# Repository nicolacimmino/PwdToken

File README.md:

# PwdToken

## Introduction

This started as a hardware implementation of a piece of paper with your password on it and, in some respect, it sill is. So use it with judgment! I toyed at first with the idea mostly of having something to type the WiFi password on new devices or for guests.

Once the novelty of the first quick implementation wore out, I started to wonder how I could make this at least reasonably secure. In its current incarnation the PwdToken offers the following features:

* Runs on a Digispark Digistump (or similart ATTiny85 device)
* Requires only 2 buttons to be soldered to the board
* Stores up to 4 passwords
* Emulates a USB keyboard and types the password
* Easy 2 buttons operation

Security features:
* Unlock password by morse keypad (optional)
* Unlock PIN by binary keypad (optional)
* Mechanism to validate count of boots and passwords recoveries (tamper/usage detection)

# Table of contents

[**Safety**](#safety)

&nbsp;&nbsp;&nbsp;&nbsp;[What makes this reasonably safe](#what-makes-this-reasonably-safe)<br>
&nbsp;&nbsp;&nbsp;&nbsp;[Known vulnerabilities](#known-vulnerabilities)<br>
&nbsp;&nbsp;&nbsp;&nbsp;[What can I do to make it safer?](#what-can-i-do-to-make-it-safer)<br>

[**Build one**](#build-one)

&nbsp;&nbsp;&nbsp;&nbsp;[The hardware](#the-hardware)<br>
&nbsp;&nbsp;&nbsp;&nbsp;[Special bootloader](#special-bootloader-optional)<br>

[**Usage**](#usage)

&nbsp;&nbsp;&nbsp;&nbsp;[Store passwords](#store-passwords)<br>
&nbsp;&nbsp;&nbsp;&nbsp;[Retrieve a password](#retrieve-a-password)<br>
&nbsp;&nbsp;&nbsp;&nbsp;[Getting the token banner](#getting-the-token-banner)<br>

[**Encase it**](#encase-it)

## Safety

Is it safe?

TLDR: **NO**

Long story. It can be reasonably safe depending on your use case. If you often need to log in on computers that are not yours and on which you can't run a password manager, this could be a viable option, especially if the alternative is to use a weak password that you can remember. At least you have shifted the extent of the potential attackers from anyone on the the Internet to anyone who can gain access to your token. 

### What makes this reasonably safe?

The passwords are stored in the actual application, and not in the data EEPROM. This means that if anyone attempts to replace the application with one that just exfiltrates the passwords then the passwords will actually be wiped.

There's a meachanism (optional) to keep track of the boots count and amount of times passwords have been retrieved. A command line application can be used to validate these against a manifest containing, among other information, a shared secret. While this doesn't prevent password theft it makes tampering evident.

### Known vulnerabilities

**do I need to say it? this is bound to be an incomplete list**

* An attacker could craft an .hex file that doesn't override the portion of code with the passwords and exfiltrates them. For this attack to be successfull it would be enough to compromise a host machine and have a microncleus uploader waiting for a device all the time (also the uploader would need to be made not to erase all memory before programming but just to send a page full of 0xFF on the part to override). This is an issue only if the stock micronucleus bootloader is used. This project provides a re-configured version of the bootloader that doesn't start unless button B (P0) is held. Additionally the special bootloader always erases user program on entry which prevents this attack also if the attacker has physical access to the token (assuming he cannot re-program it with an AVR programmer, ie that the board is encased in epoxy and only USB pins are accessible).

* An attacker could connect an AVR programmer and dump the application or replace the bootloader with one that exfiltrates the passwords. This is possible only if the attacker has physical access to the token. This can be mitigated by enclosing the devive in epoxy so that only the USB pins are accessible. While the attacker could still possibly re-program it, this would require access to the device for a longer time and the tampering would be evident.

* Because of the way the password lock works (just waits until the right PIN/Password is entered), and because the onboard LED signals the fact the token is locked, an attacker could build a device that brute forces the PIN/Password quite easily. One possible mitigating action would be to add a max errors after which the device wipes itself. Also in this case physical access to the device is needed to carry out this attack so epoxying the board would suffice.

### What can I do to make it safer?

* Make use of the provided modified bootloader so the device cannot be re-programmed without physical access to it and, even if bootloader is entered, the program is wiped already
* Don't store the full password, use a Horcrux (in a nutshell, make your password something like `fsnf23m!abcSomethingIOnlyKnow` and only store the `fsnf23m!abc` part to then type the reminder)
* Don't leave the token unattended and keep track of your tokens so you can immediately reset the passwords if one is missing
* Encase the device in epoxy so only the USB pins are accessible. This prevents PIN brute force automation as well as bootloaded replacement.

## Build one

### The hardware

If you want to just give this a spin a quick way to start is with a Digispark Digistump or another ATTiny85 board with USB. You will need to add two push buttons. Connect them between P0 and P2 and ground. See photo for one of my prototypes.

If you feel instead like wire wrapping and you have a DIP ATTiny85 you can follow this schematic. J2 is needed only if you need to burn a bootloader, if your ATTiny is already loaded with a bootloader you can omit it.

Alternatively, if you really want to go serious you can find all the Kicad files for the board in the `Board` folder.

### Special bootloader (optional)

You can replace the standard "micronucleus" bootloader that comes with the Digistump and other ATTiny borards, with a version that doesn't wait in the bootloader by default when started. This makes your PwdToken immediately available when plugging it. Once you uploaded the re-configured bootloader you will need to pull P0 low (press button B before inserting the board in the USB port). To carry out this step you will need an ISP. I tested this with a USBASP. Others shouldn't be that much different but you will need to tweak the actual programming command. 

If you choose to skip this step the downside will be that once you plug your board in the USB port you will need to wait about 6 seconds for the bootloader to give up and your program to start.

Another tweak to the bootloader that can make the device safer, is to enable deletion of the user program as soon as it's  the bootloader is entered. In this way it won't be possible in any way to attempt to exfiltrate the passwords through USB. 

**NOTE**: it will be still possible to get to them if the attacker has access to all pins (device not epoxied) as he will be able to replace the bootloader.

See the readme in the "mirconucleus" folder below for instructions on building and flashing the special bootloader.

## Usage

### Store passwords 

**Without manifest**

If you wish to just set up passwords and don't want to generate a manifest to verify the integrity of the token (and to have proof the token has not been used) follow these simple steps:

* Copy `secrets_example.h` to `secrets.h` (this last is .gitignore:d so you don't risk to push your passwords!)
* Edit `secrets.h` and set your passwords and unlock password/pin if desired
* Edit `options.h` and set options as needed 
* Build and upload

**With manifest**

If you choose to generate a manifest for the token you will be able at a later time to verify that the token has not been tampered with and you will be able to determine if and how many times it has been booted and passwords have been retrieved.

To generate a manifest use the command line utility under `CommandLineTool\bin`:

* Run `pwdtoken gen`
* Choose a label for the token
* Choose a secret
* The utility will generate a manifest and store in clipboard
* Store the manifest somewhere safe (eg a password manager)
* The utility will also generate a `secrets.h` file
* Edit `secrets.h` and set your passwords and unlock password/pin if desired (don't change the OTP secret or the label though or you will invalidate the manifest!)
* Edit `options.h` and set options as needed 
* Build and upload

## Retrieve a Password

**note** the token emulates a standard US layout keyboard. You will need to make sure your keyboard layout matches, especially if your password contains symbols that might be mapped to different keys.

* Insert the token in a USB port and wait until the onboard red LED is solid red (or flashing slowly if you choose not to have an unlock PIN/Password)
* Type your PIN/Password if needed
* Once unlocked the onboard red LED will start to flash. The flashes count indicates the selected password
* Press repeatedly button B until the desired password is selected
* Focus on the application/field in which you need to type the password
* Press and hold A for more than 2 seconds and the password will by typed

## Getting the token banner

The token banner is a piece of formatted text that contains non-confidential information and can be used to validate the boot counts as well as to make sure your keyboard layout is correct. The banner is always accessible without unlocking the token. To print the banner follow these steps:

* Open a text editor and ensure it's in focus
* Insert the token while keeping button A pressed (make sure you don't confuse A with B if you have the special bootloader or your passwords will be lost!)
* Release the button as soon as the banner is starting to appear

A banner looks like this:

````
----------- begin -----------

; PwdToken 0.01-B
; Built Apr 14 2021 07:27:29
; Keyboard Layout US
; Hash Backslash: £ #
LBL: TST002
CBO: 3
CRE: 0
OTP: 3158792869

------------ end ------------
````

You can use the `; Hash Backslash: # \` line to validate that the current keyboard layout is correct. Most of the rest of the information in the banner is data needed by the command line utility to validate the boot and password retrieval counters.

## Encase it

In the `case` folder you will find a FreeCad project for a simple case for the token. This is suitable to be filled with epoxy to prevent (easy) access to the passwords through the ISP interface. There's no provision for screws or other fixing mechanisms, the two halves of the shell are meant to be glued together once the epoxy is set.

Top             |  Bottom    | Assembled
:-------------------------:|:-------------------------:|:-------------------------:
  |   |

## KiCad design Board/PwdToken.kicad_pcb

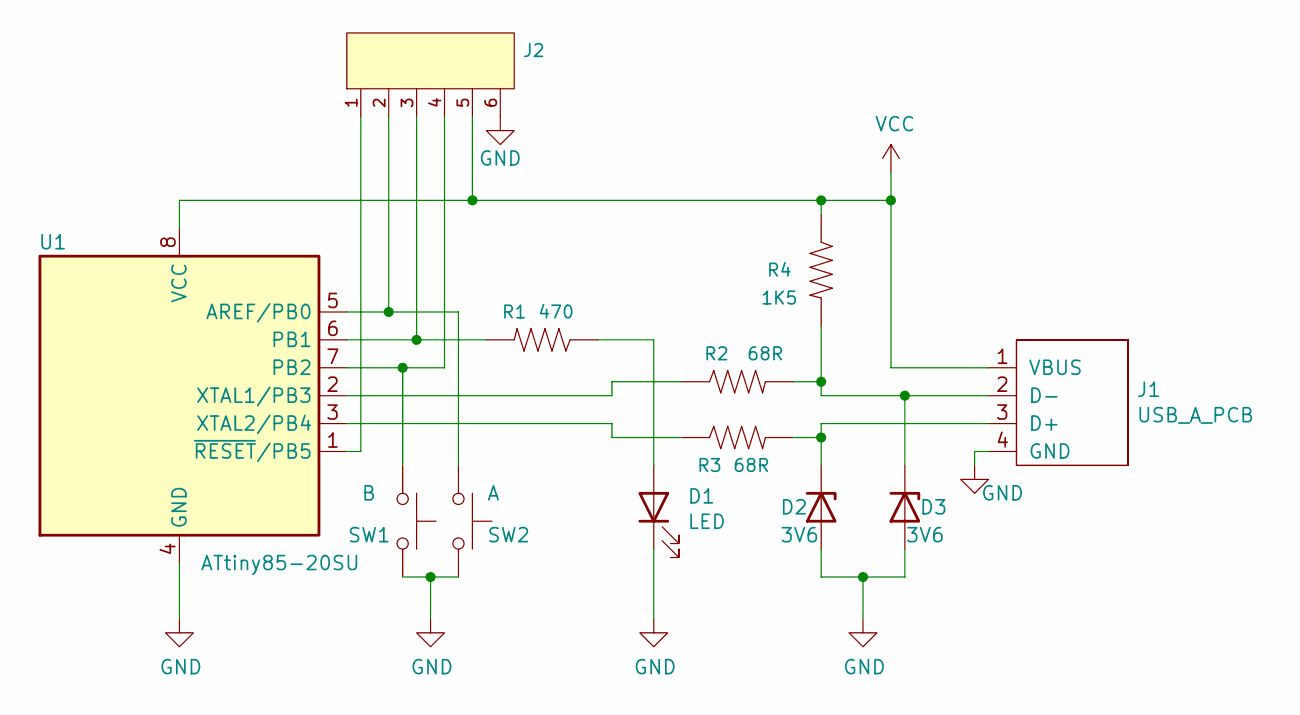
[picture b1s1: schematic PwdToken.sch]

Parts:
D1: LED; LED_0805_2012Metric_Pad1.15x1.40mm_HandSolder
D2, D3: 3V6; D_SOD-128
J1: USB_A_PCB; usb-PCB
J2: JST_6_PIN_VERTICAL; 1X06
R1: 470; R_0805_2012Metric_Pad1.20x1.40mm_HandSolder
R2, R3: 68R; R_0805_2012Metric_Pad1.20x1.40mm_HandSolder
R4: 1K5; R_0805_2012Metric_Pad1.20x1.40mm_HandSolder
SW1: A; SW_Tactile_Straight_KSA0Axx1LFTR
SW2: B; SW_Tactile_Straight_KSA0Axx1LFTR
U1: ATtiny85-20SU; SOIC-8_3.9x4.9mm_P1.27mm

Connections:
GND: D1.1 (K), D2.2 (A), D3.2 (A), J1.4 (GND), J2.6, SW1.2, SW2.2, U1.4 (GND)
unnamed: D1.2 (A), R1.1
unnamed: D2.1 (K), J1.3 (D+), R3.2
unnamed: D3.1 (K), J1.2 (D-), R2.2, R4.2
unnamed: J2.1, U1.1 (~RESET~/PB5)
unnamed: J2.2, SW2.1, U1.5 (AREF/PB0)
unnamed: J2.3, R1.2, U1.6 (PB1)
unnamed: J2.4, SW1.1, U1.7 (PB2)
unnamed: R2.1, U1.2 (XTAL1/PB3)
unnamed: R3.1, U1.3 (XTAL2/PB4)
VCC: J1.1 (VBUS), J2.5, R4.1, U1.8 (VCC)

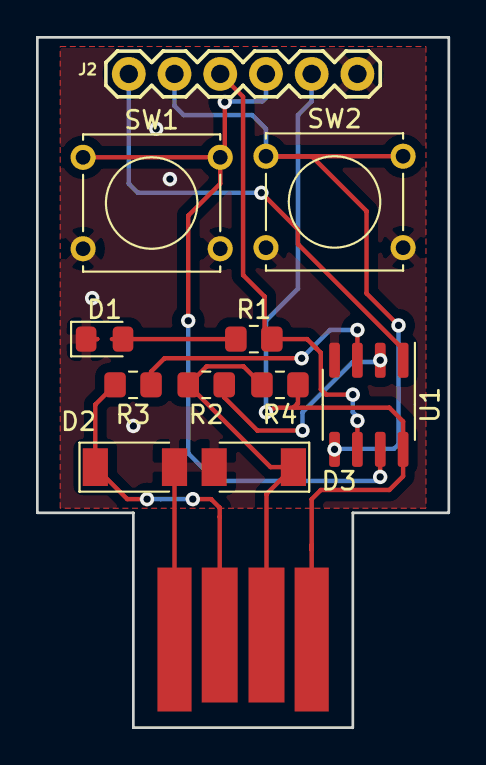
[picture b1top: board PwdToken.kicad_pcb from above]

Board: 2 copper layers, 22.9 x 38.4 mm, 12 parts (0 on the bottom side), 11 nets.

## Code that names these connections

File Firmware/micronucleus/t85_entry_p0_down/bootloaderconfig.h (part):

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 *
 * Controller type: ATtiny 85 - 16.5 MHz
 * Configuration:   Default configuration
 *       USB D- :   PB3
 *       USB D+ :   PB4
 *       Entry  :   Always
 *       LED    :   None
 *       OSCCAL :   Stays at 16 MHz
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 *                      external jumper.
 *                      Adds 34 bytes.
 *
 *       JUMPER_PIN     Pin the jumper is connected to. (e.g. PB0)
 *       JUMPER_PORT    Port out register for the jumper (e.g. PORTB)
 *       JUMPER_DDR     Port data direction register for the jumper (e.g. DDRB)
 *       JUMPER_INP     Port input register for the jumper (e.g. PINB)
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 *
 */

#define JUMPER_PIN    PB0
#define JUMPER_PORT   PORTB
#define JUMPER_DDR    DDRB
#define JUMPER_INP    PINB
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
#define LED_DDR     DDRB
#define LED_PORT    PORTB
#define LED_PIN     PB1

/*
 *  This is the implementation of the LED code. Change the configuration above unless you want to
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
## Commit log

2021-03-20 First implementation
2021-03-20 Break the seal
2021-03-20 Refactor, don't always print banner
2021-03-20 Add LED
2021-03-20 Cleanup
2021-03-28 Change to CRC
2021-03-28 Change seal for a OTP based on boot and type count
2021-03-28 Update secrets exmple
2021-03-30 Add utility to validate token OTP
2021-03-31 Validate both otps
2021-03-31 Refactor
2021-04-02 Sandwich counter between secret
2021-04-02 More go like error handling
2021-04-02 Add multi passwords
2021-04-02 Flash current password index
2021-04-03 better flasher
2021-04-06 Better error
2021-04-06 Rename
2021-04-06 Comments
2021-04-07 Added generator
2021-04-10 Massive refactoring
2021-04-10 Bettwer hw config and button B added
2021-04-10 Renamed folder
2021-04-10 Reset example manifest to 0 counters
2021-04-10 Add unlock password
2021-04-10 Swap pins
2021-04-10 Add micronucleus modified config
2021-04-10 Provide pre-built micronucleus with entry on p0 down
2021-04-11 better banner
2021-04-11 Add binary keyboard
2021-04-11 Shuffle
2021-04-11 Rename readme.md to README.md
2021-04-11 ups, don't spill the secret!
2021-04-12 Clean
2021-04-12 Add some delay before printing the banner
2021-04-12 Swap A/B naming, keep same pins, makes more sense when looking at the device plugged in
2021-04-12 Rotate and label
2021-04-13 output counters, single OTP, don't boot after banner
2021-04-13 Adapt to new banner format
2021-04-13 Fix header generation
2021-04-13 Write header
2021-04-13 Update message
2021-04-13 Update h template
2021-04-14 Update samples
2021-04-14 Cast incremented value
2021-04-20 Add patch for micronucleus safe boot
2021-04-20 Fix readme
2021-04-21 Add failed logins counter
2021-04-22 Add unlock reset count
2021-04-23 Self destruct on max failed login exceeded
2021-04-24 Add board
2021-04-25 Add model render
2021-04-25 Update to white board
2021-04-26 Add schematic
2021-04-27 Add web skeleton
2021-04-29 toy around with css
2021-05-09 Add case
2021-05-09 Better renders
2021-05-09 trim
2021-05-09 Make all images same size
2021-05-09 Fix board USB connector size

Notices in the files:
Firmware/micronucleus/t85_entry_p0_down/bootloaderconfig.h:
License: GNU GPL v2 (see License.txt
